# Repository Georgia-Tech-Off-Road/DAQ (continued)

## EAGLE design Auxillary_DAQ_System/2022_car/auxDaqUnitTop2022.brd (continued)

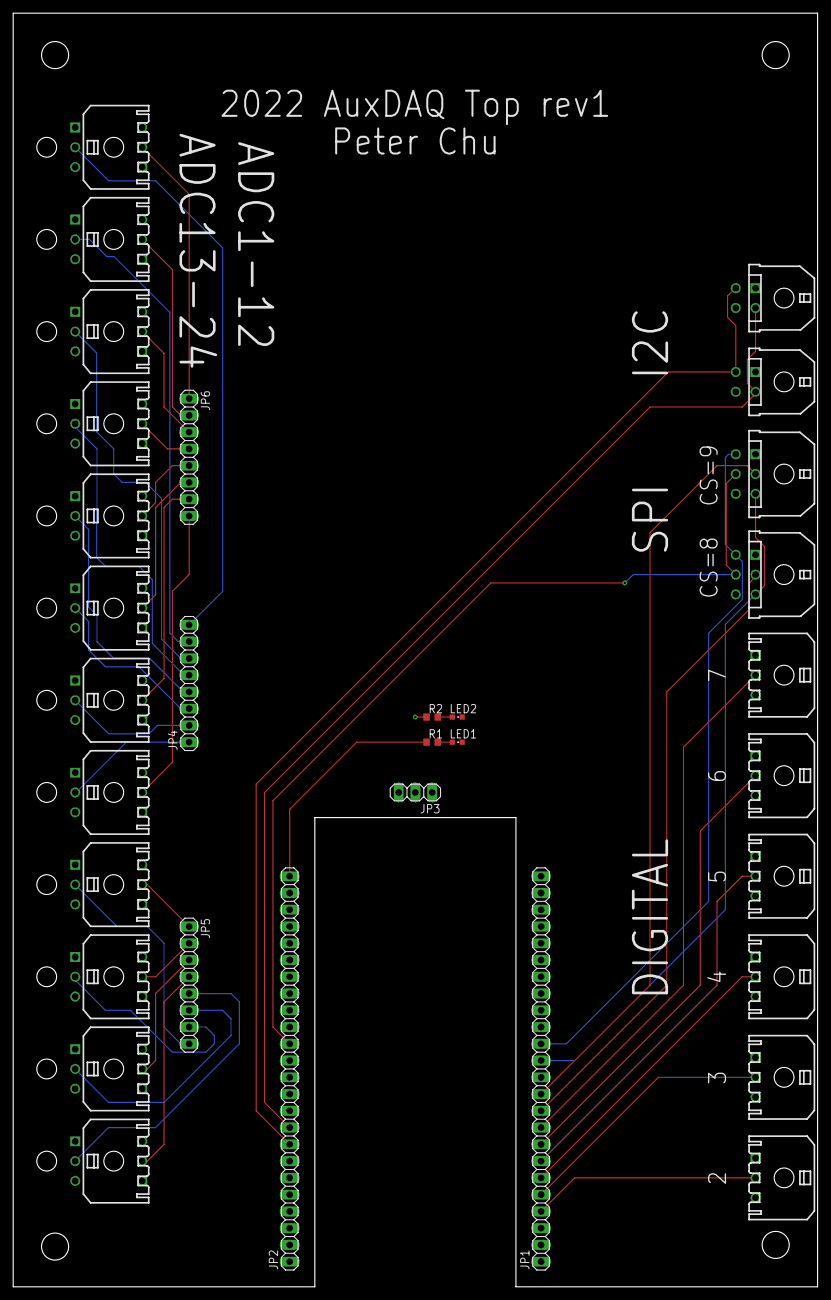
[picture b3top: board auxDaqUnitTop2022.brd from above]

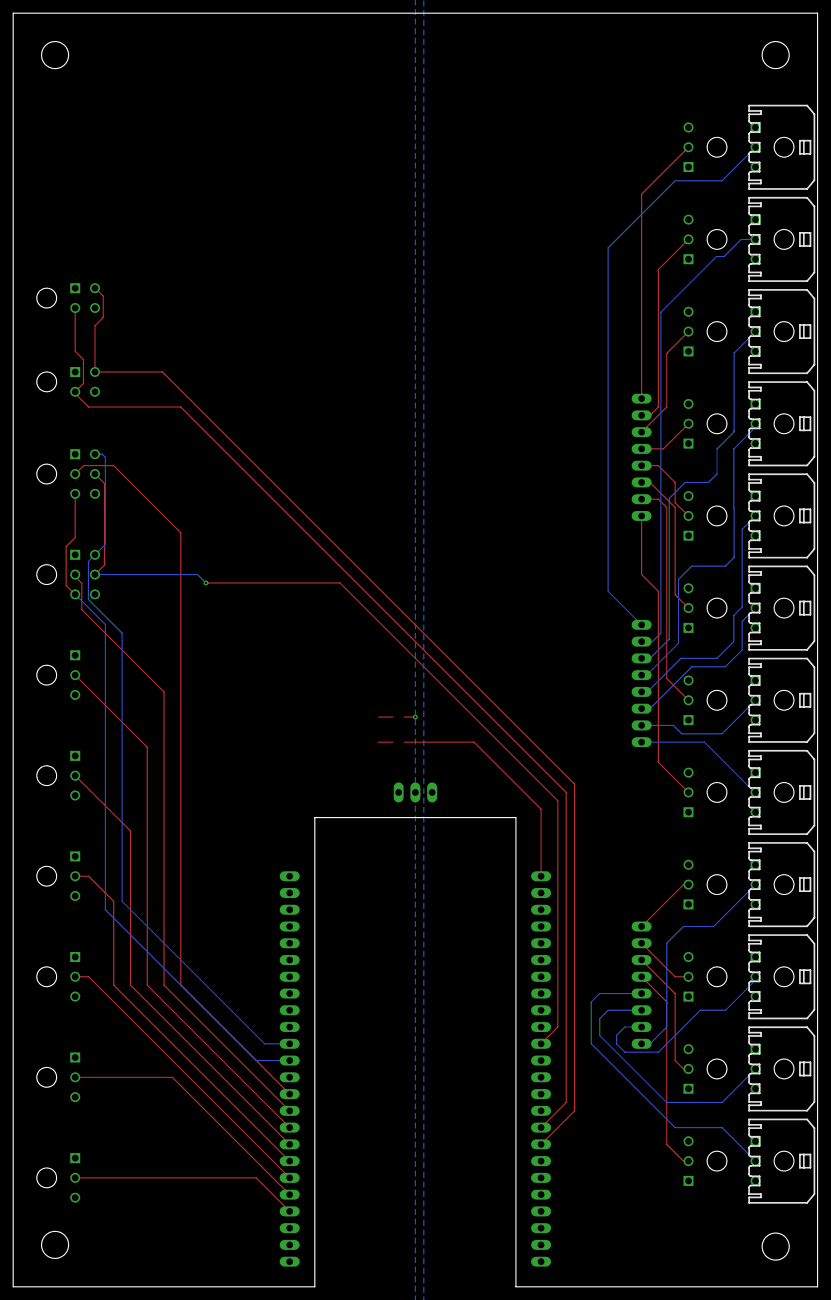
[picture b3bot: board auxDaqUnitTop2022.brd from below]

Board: 2 copper layers, 121.9 x 193.0 mm, 44 parts (12 on the bottom side), 43 nets.

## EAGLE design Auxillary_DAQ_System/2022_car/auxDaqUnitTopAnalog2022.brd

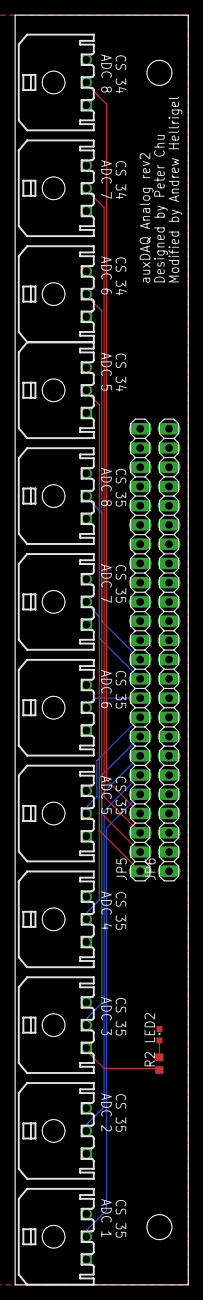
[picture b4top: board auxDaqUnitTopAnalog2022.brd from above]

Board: 2 copper layers, 22.9 x 167.6 mm, 16 parts (0 on the bottom side), 15 nets.

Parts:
A12, A13, A14, A15, A16, A17, A18, A19, A20, A21, A22, A23: 43650-0300
JP5, JP6: 1X24
LED2: GREEN; LED-603
R2: 220; R0603

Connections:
+5V: A12.P$1, A13.P$1, A14.P$1, A15.P$1, A16.P$1, A17.P$1, A18.P$1, A19.P$1, A20.P$1, A21.P$1, A22.P$1, A23.P$1, JP6.1, R2.1
ADC13: A12.P$2, JP5.1
ADC14: A13.P$2, JP5.2
ADC15: A14.P$2, JP5.3
ADC16: A15.P$2, JP5.4
ADC17: A16.P$2, JP5.5
ADC18: A17.P$2, JP5.6
ADC19: A18.P$2, JP5.7
ADC20: A19.P$2, JP5.8
ADC21: A20.P$2, JP5.9
ADC22: A21.P$2, JP5.10
ADC23: A22.P$2, JP5.11
ADC24: A23.P$2, JP5.12
GND: A12.P$3, A13.P$3, A14.P$3, A15.P$3, A16.P$3, A17.P$3, A18.P$3, A19.P$3, A20.P$3, A21.P$3, A22.P$3, A23.P$3, JP6.2, JP6.15, LED2.C
unnamed: LED2.A, R2.2

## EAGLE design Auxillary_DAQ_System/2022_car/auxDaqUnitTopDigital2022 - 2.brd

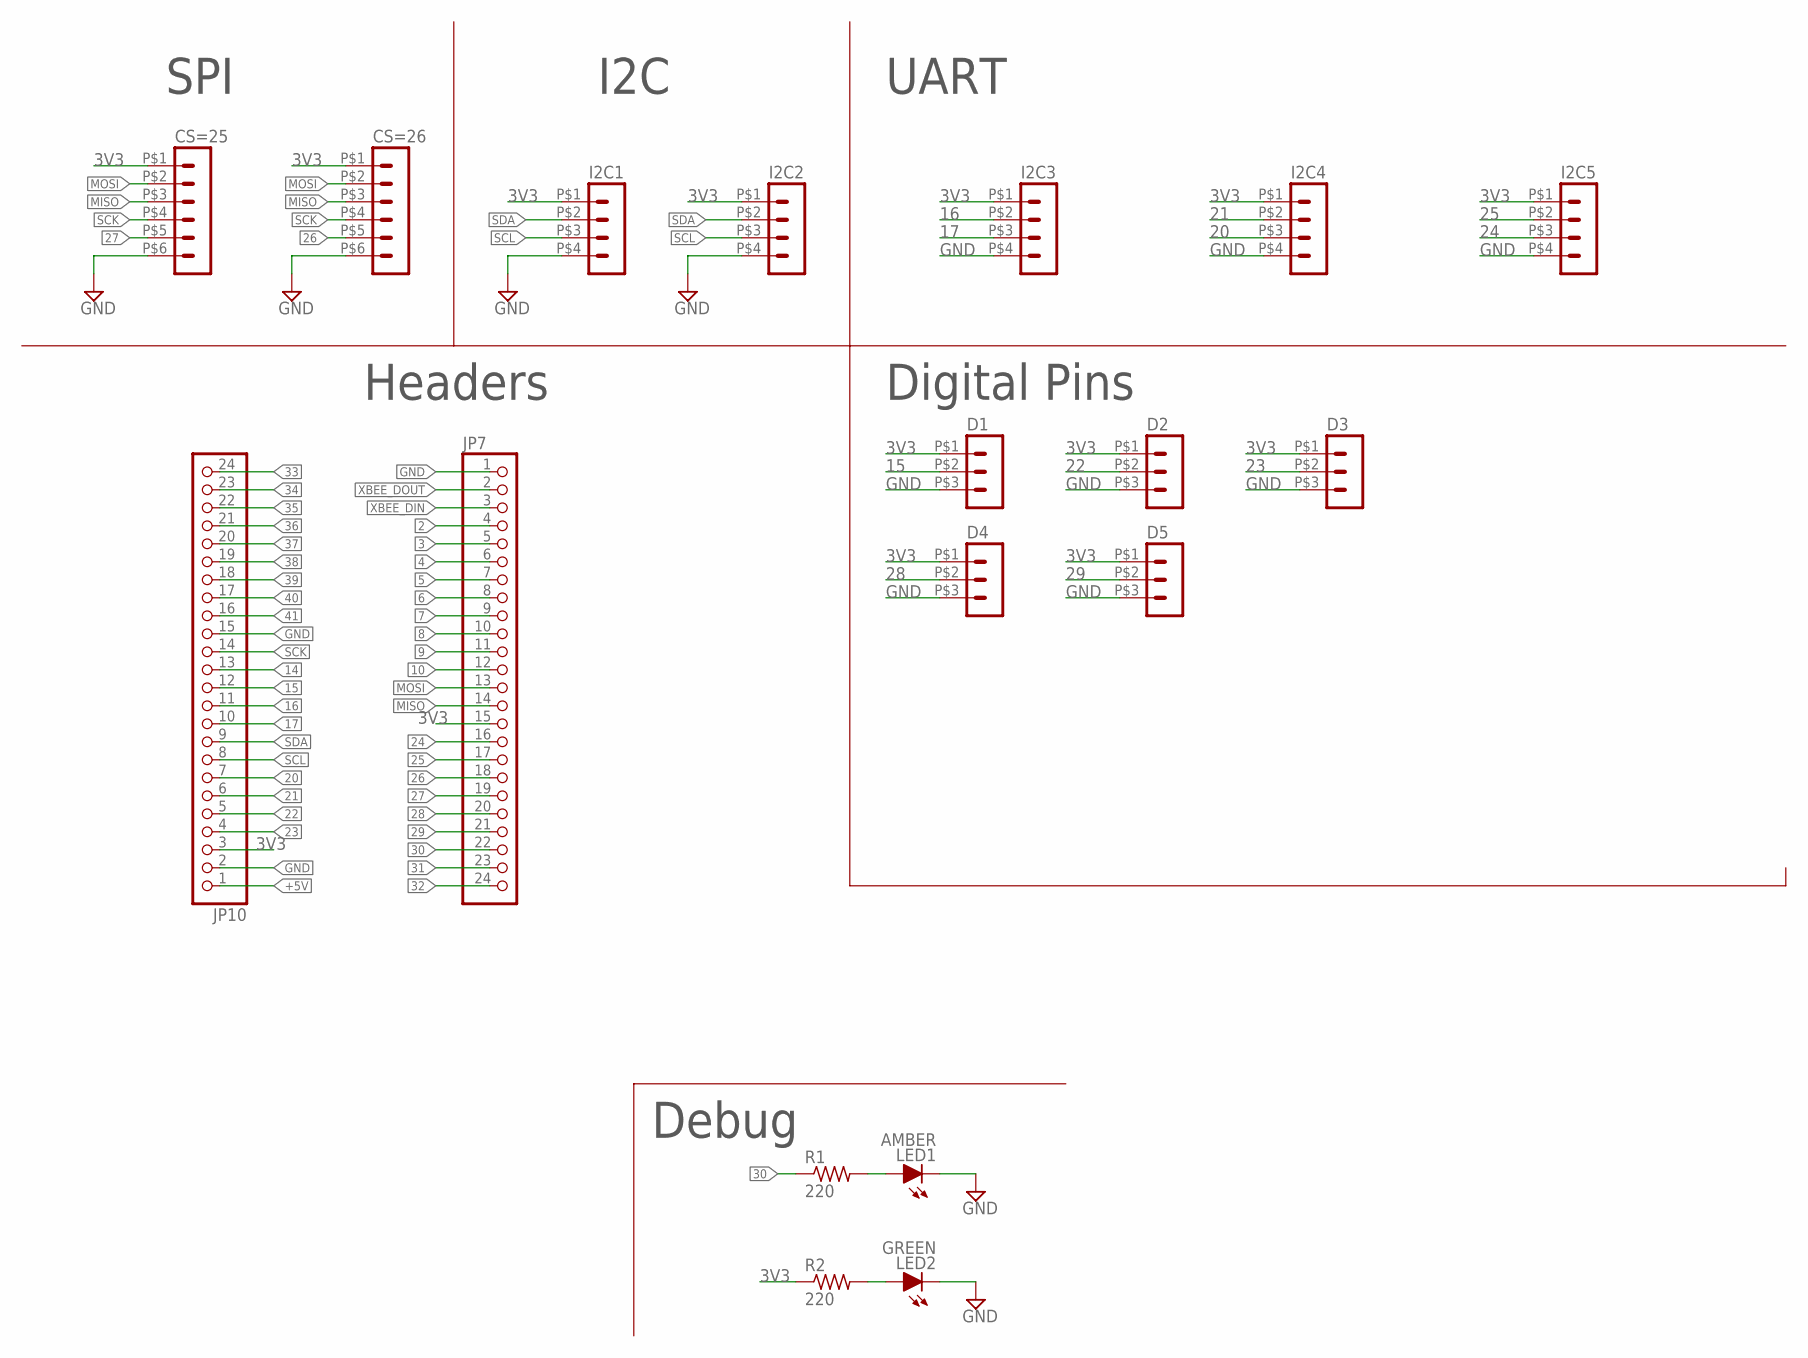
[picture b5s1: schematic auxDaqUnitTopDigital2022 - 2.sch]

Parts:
CS=25, CS=26: HEADER_POS6_43045-0600; 43045-0600
D1, D2, D3, D4, D5: HEADER_POS3_43650-0300; 43650-0300
I2C1, I2C2, I2C3, I2C4, I2C5: HEADER_POS4_43045-0401; 43045-0400
JP7, JP10: PINHD-1X24; 1X24
LED1: AMBER; LED-603
LED2: GREEN; LED-603
R1, R2: 220; R0603

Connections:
2: JP7.4
3: JP7.5
3V3: CS=25.P$1 (1), CS=26.P$1 (1), D1.P$1 (1), D2.P$1 (1), D3.P$1 (1), D4.P$1 (1), D5.P$1 (1), I2C1.P$1 (1), I2C2.P$1 (1), I2C3.P$1 (1), I2C4.P$1 (1), I2C5.P$1 (1), JP7.15, JP10.3, R2.1
4: JP7.6
5: JP7.7
6: JP7.8
7: JP7.9
8: JP7.10
9: JP7.11
10: JP7.12
14: JP10.13
15: D1.P$2 (2), JP10.12
16: I2C3.P$2 (2), JP10.11
17: I2C3.P$3 (3), JP10.10
20: I2C4.P$3 (3), JP10.7
21: I2C4.P$2 (2), JP10.6
22: D2.P$2 (2), JP10.5
23: D3.P$2 (2), JP10.4
24: I2C5.P$3 (3), JP7.16
25: I2C5.P$2 (2), JP7.17
26: CS=26.P$5 (5), JP7.18
27: CS=25.P$5 (5), JP7.19
28: D4.P$2 (2), JP7.20
29: D5.P$2 (2), JP7.21
30: JP7.22, R1.1
31: JP7.23
32: JP7.24
33: JP10.24
34: JP10.23
35: JP10.22
36: JP10.21
37: JP10.20
38: JP10.19
39: JP10.18
40: JP10.17
41: JP10.16
+5V: JP10.1
GND: CS=25.P$6 (6), CS=26.P$6 (6), D1.P$3 (3), D2.P$3 (3), D3.P$3 (3), D4.P$3 (3), D5.P$3 (3), I2C1.P$4 (4), I2C2.P$4 (4), I2C3.P$4 (4), I2C4.P$4 (4), I2C5.P$4 (4), JP7.1, JP10.2, JP10.15, LED1.C, LED2.C
MISO: CS=25.P$3 (3), CS=26.P$3 (3), JP7.14
MOSI: CS=25.P$2 (2), CS=26.P$2 (2), JP7.13
unnamed: LED1.A, R1.2
unnamed: LED2.A, R2.2
SCK: CS=25.P$4 (4), CS=26.P$4 (4), JP10.14
SCL: I2C1.P$3 (3), I2C2.P$3 (3), JP10.8
SDA: I2C1.P$2 (2), I2C2.P$2 (2), JP10.9
XBEE_DIN: JP7.3
XBEE_DOUT: JP7.2

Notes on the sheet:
Headers
SPI
I2C
Digital Pins
Debug
UART

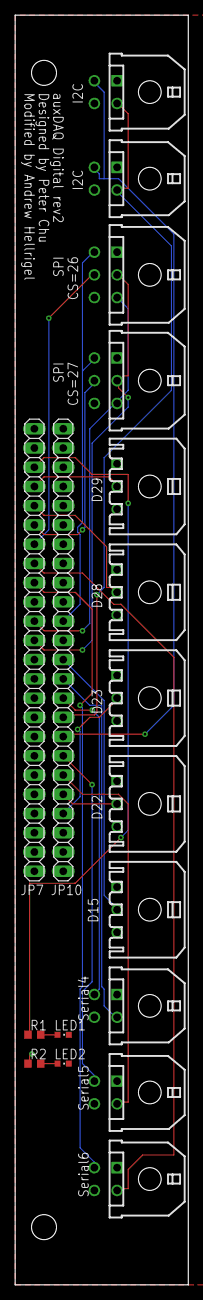
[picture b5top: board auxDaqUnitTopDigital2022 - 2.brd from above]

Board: 2 copper layers, 22.9 x 167.6 mm, 18 parts (0 on the bottom side), 23 nets.

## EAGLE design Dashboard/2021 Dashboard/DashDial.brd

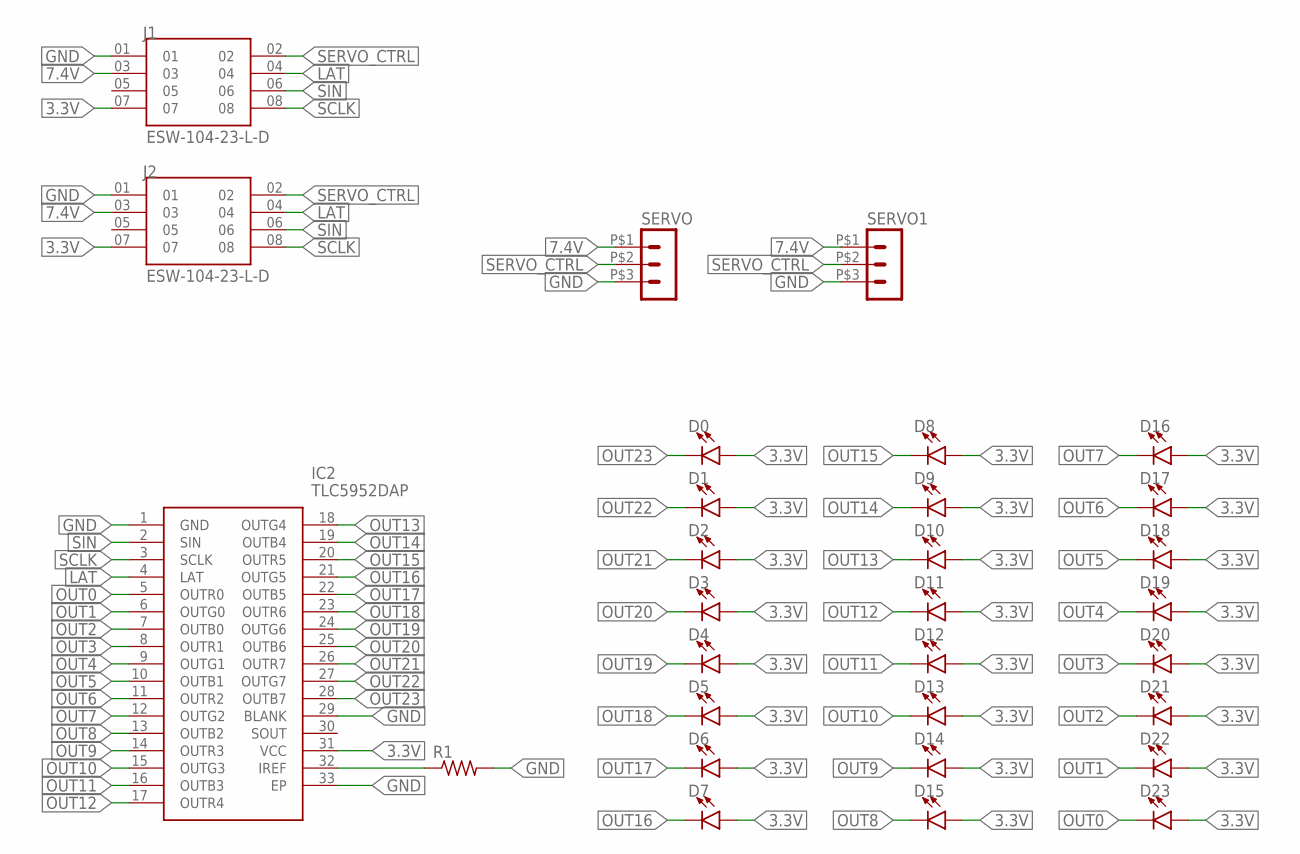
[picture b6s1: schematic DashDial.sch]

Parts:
D0, D1, D2, D3, D4, D5, D6, D7, D8, D9, D10, D11, D12, D13, D14, D15, D16, D17, D18, D19, D20, D21, D22, D23: LED3MM; LED_3MM
IC2: TLC5952DAP; SOP65P810X120-33N
J1, J2: ESW-104-23-L-D; SAMTEC_ESW-104-23-L-D
R1: RES_SMDR0603; R0603
SERVO, SERVO1: HEADER_POS3_43650-0300; 43650-0300

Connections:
3.3V: D0.A, D1.A, D2.A, D3.A, D4.A, D5.A, D6.A, D7.A, D8.A, D9.A, D10.A, D11.A, D12.A, D13.A, D14.A, D15.A, D16.A, D17.A, D18.A, D19.A, D20.A, D21.A, D22.A, D23.A, IC2.31 (VCC), J1.07, J2.07
7.4V: J1.03, J2.03, SERVO.P$1 (1), SERVO1.P$1 (1)
GND: IC2.1 (GND), IC2.29 (BLANK), IC2.33 (EP), J1.01, J2.01, R1.2, SERVO.P$3 (3), SERVO1.P$3 (3)
LAT: IC2.4 (LAT), J1.04, J2.04
unnamed: IC2.32 (IREF), R1.1
OUT0: D23.K (C), IC2.5 (OUTR0)
OUT1: D22.K (C), IC2.6 (OUTG0)
OUT2: D21.K (C), IC2.7 (OUTB0)
OUT3: D20.K (C), IC2.8 (OUTR1)
OUT4: D19.K (C), IC2.9 (OUTG1)
OUT5: D18.K (C), IC2.10 (OUTB1)
OUT6: D17.K (C), IC2.11 (OUTR2)
OUT7: D16.K (C), IC2.12 (OUTG2)
OUT8: D15.K (C), IC2.13 (OUTB2)
OUT9: D14.K (C), IC2.14 (OUTR3)
OUT10: D13.K (C), IC2.15 (OUTG3)
OUT11: D12.K (C), IC2.16 (OUTB3)
OUT12: D11.K (C), IC2.17 (OUTR4)
OUT13: D10.K (C), IC2.18 (OUTG4)
OUT14: D9.K (C), IC2.19 (OUTB4)
OUT15: D8.K (C), IC2.20 (OUTR5)
OUT16: D7.K (C), IC2.21 (OUTG5)
OUT17: D6.K (C), IC2.22 (OUTB5)
OUT18: D5.K (C), IC2.23 (OUTR6)
OUT19: D4.K (C), IC2.24 (OUTG6)
OUT20: D3.K (C), IC2.25 (OUTB6)
OUT21: D2.K (C), IC2.26 (OUTR7)
OUT22: D1.K (C), IC2.27 (OUTG7)
OUT23: D0.K (C), IC2.28 (OUTB7)
SCLK: IC2.3 (SCLK), J1.08, J2.08
SERVO_CTRL: J1.02, J2.02, SERVO.P$2 (2), SERVO1.P$2 (2)
SIN: IC2.2 (SIN), J1.06, J2.06

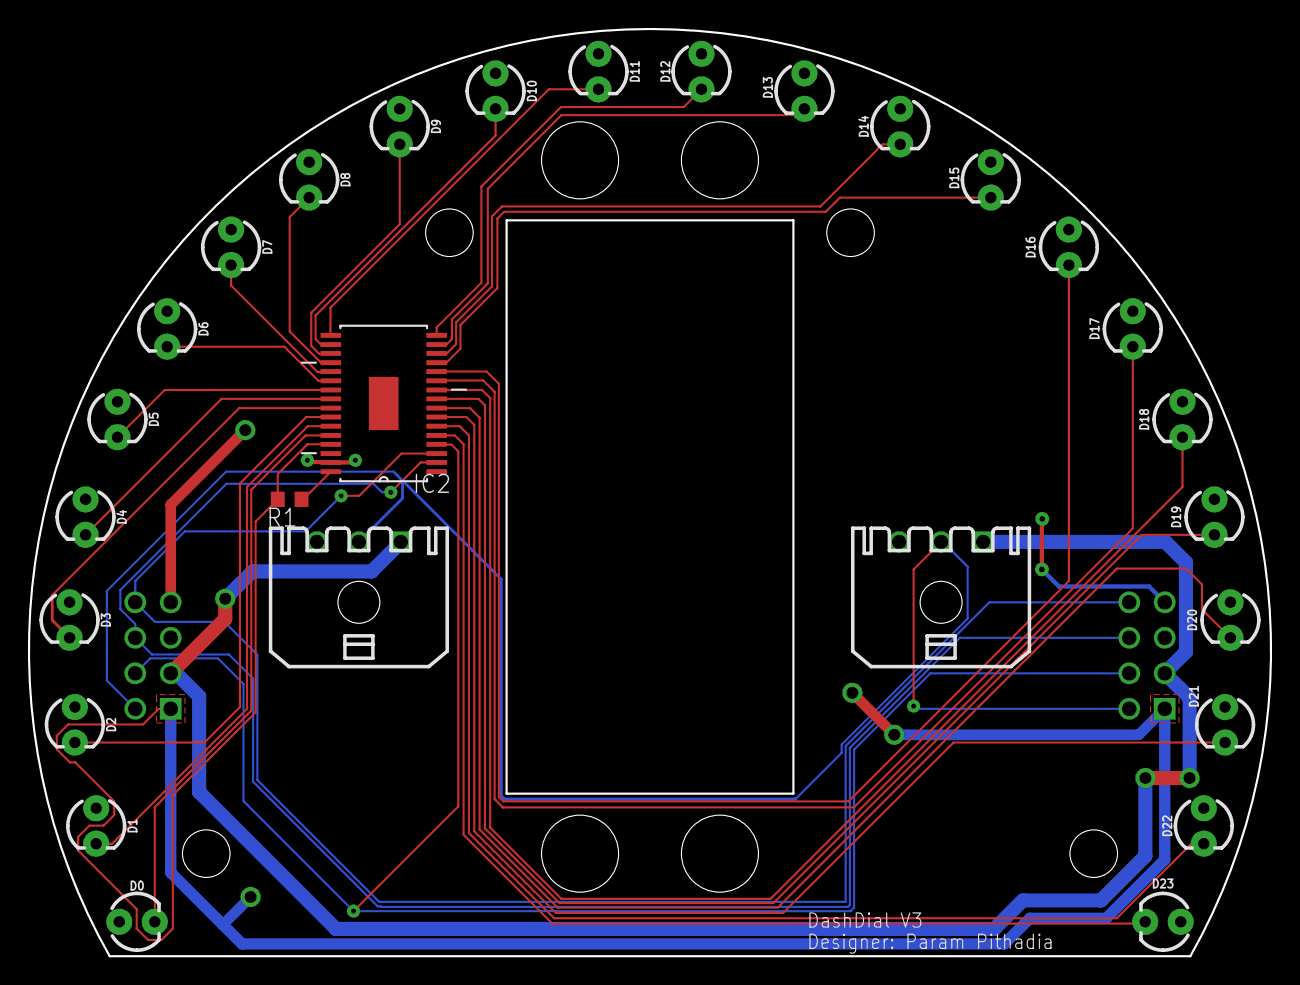
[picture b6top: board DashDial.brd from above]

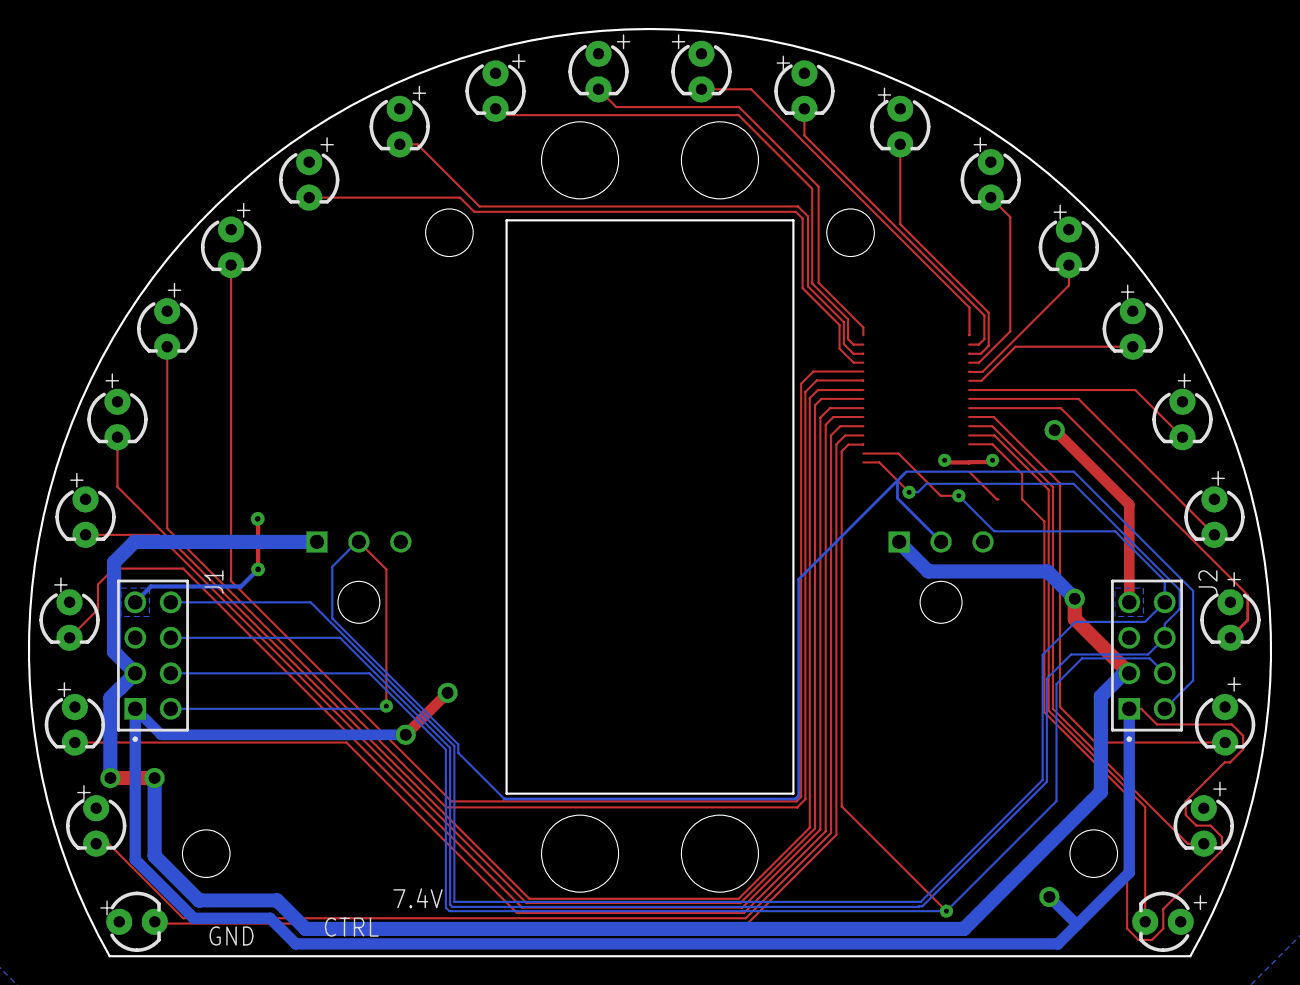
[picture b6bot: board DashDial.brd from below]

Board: 2 copper layers, 88.9 x 66.3 mm, 30 parts (2 on the bottom side), 32 nets.

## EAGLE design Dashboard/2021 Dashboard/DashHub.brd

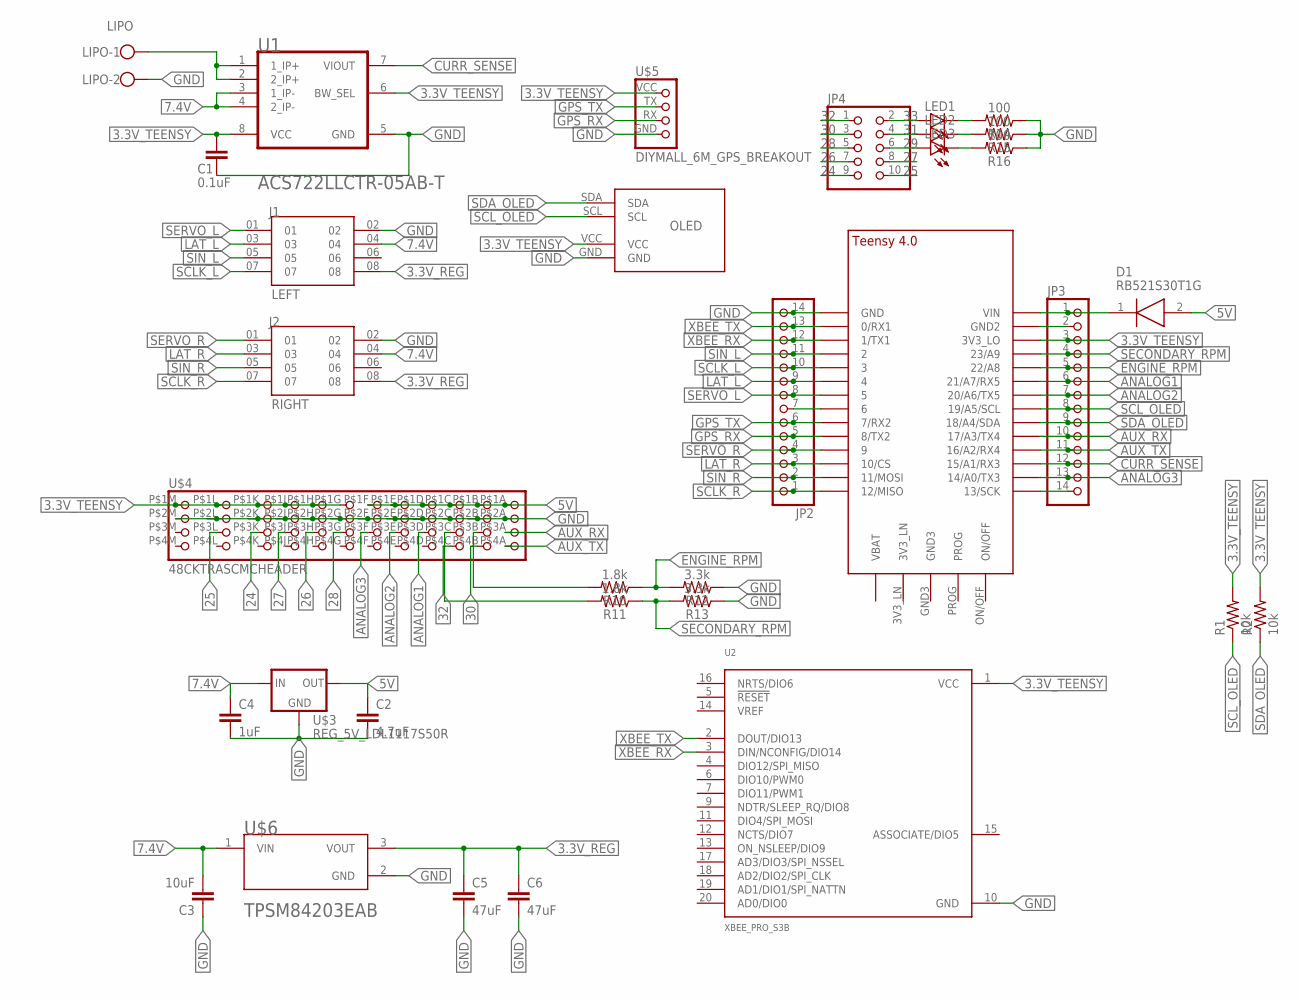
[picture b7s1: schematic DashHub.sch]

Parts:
C1: 0.1uF; C0402
C2: 4.7uF; C0603
C3: 10uF; C1206
C4: 1uF; C1206
C5, C6: 47uF; C1206
D1: RB521S30T1G; SODFL1608X70N
J1: LEFT; SAMTEC_ESW-104-23-L-D
J2: RIGHT; SAMTEC_ESW-104-23-L-D
JP2, JP3: PINHD-1X14; 1X14
JP4: PINHD-2X5; 2X05
LED1, LED2, LED3: LEDCHIPLED_1206; CHIPLED_1206
LIPO: LIPO; W237-102
R1, R2: 10k; R0603
R10, R11: 1.8k; AXIAL-0.3
R12, R13: 3.3k; AXIAL-0.3
R14, R15, R16: 100; AXIAL-0.3
U1: ALLEGRO_MICROSYSTEMS_ACS722LLCTR-05AB-TALLEGRO_MI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; ALLEGRO_MICROSYSTEMS_ACS722LLCTR-05AB-T_0
U2: XBEE_PRO_S3B
U$1: TEENSY_4.0-BASIC
U$2: OLED_SSD1306
U$3: REG_5V_LDL1117S50R; SOT230P700X180-4N
U$4: 48CKTRASCMCHEADER
U$5: DIYMALL_6M_GPS_BREAKOUT
U$6: TPSM84205EAB

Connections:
3.3V_REG: C5.1, C6.1, J1.08, J2.08, U$6.3 (VOUT)
3.3V_TEENSY: C1.2, JP3.3, R1.2, R2.2, U1.6 (BW_SEL), U1.8 (VCC), U2.1 (VCC), U$1.3V3_LO, U$2.VCC, U$4.P$1G (1G), U$4.P$1H (1H), U$4.P$1J (1J), U$4.P$1K (1K), U$4.P$1L (1L), U$4.P$1M (1M), U$5.VCC
5V: C2.1, D1.2 (A), U$3.2 (OUT), U$3.4 (OUT), U$4.P$1A (1A), U$4.P$1B (1B), U$4.P$1C (1C), U$4.P$1D (1D), U$4.P$1E (1E), U$4.P$1F (1F)
7.4V: C3.2, C4.1, J1.04, J2.04, U1.3 (1_IP-), U1.4 (2_IP-), U$3.3 (IN), U$6.1 (VIN)
24: JP4.9, U$4.P$3K (3K)
25: JP4.10, U$4.P$3L (3L)
26: JP4.7, U$4.P$3H (3H)
27: JP4.8, U$4.P$3J (3J)
28: JP4.5, U$4.P$3G (3G)
29: JP4.6, LED3.A
30: JP4.3, U$4.P$4B (4B)
31: JP4.4, LED2.A
32: JP4.1, U$4.P$4C (4C)
33: JP4.2, LED1.A
ANALOG1: JP3.6, U$1.21/A7 (21/A7/RX5), U$4.P$3D (3D)
ANALOG2: JP3.7, U$1.20/A6 (20/A6/TX5), U$4.P$3E (3E)
ANALOG3: JP3.13, U$1.14/A0 (14/A0/TX3), U$4.P$3F (3F)
AUX_RX: JP3.10, U$1.17/A3 (17/A3/TX4), U$4.P$3A (3A)
AUX_TX: JP3.11, U$1.16/A2 (16/A2/RX4), U$4.P$4A (4A)
CURR_SENSE: JP3.12, U1.7 (VIOUT), U$1.15/A1 (15/A1/RX3)
ENGINE_RPM: JP3.5, R10.P$1 (1), R12.P$2 (2), U$1.22/A8
GND: C1.1, C2.2, C3.1, C4.2, C5.2, C6.2, J1.02, J2.02, JP2.14, LIPO.2, R12.P$1 (1), R13.P$1 (1), R14.P$1 (1), R15.P$1 (1), R16.P$1 (1), U1.5 (GND), U2.10 (GND), U$1.GND, U$2.GND, U$3.1 (GND), U$4.P$2A (2A), U$4.P$2B (2B), U$4.P$2C (2C), U$4.P$2D (2D), U$4.P$2E (2E), U$4.P$2F (2F), U$4.P$2G (2G), U$4.P$2H (2H), U$4.P$2J (2J), U$4.P$2K (2K), U$4.P$2L (2L), U$4.P$2M (2M), U$5.GND, U$6.2 (GND)
GND2: JP3.2, U$1.GND2
GPS_RX: JP2.5, U$1.8 (8/TX2), U$5.RX
GPS_TX: JP2.6, U$1.7 (7/RX2), U$5.TX
LAT_L: J1.03, JP2.9, U$1.4/CANRX (4)
LAT_R: J2.03, JP2.3, U$1.10/CS
LIPO_IN: LIPO.1, U1.1 (1_IP+), U1.2 (2_IP+)
unnamed: JP2.7, U$1.6
unnamed: D1.1 (K), JP3.1, U$1.VIN
unnamed: LED1.C, R14.P$2 (2)
unnamed: LED2.C, R15.P$2 (2)
unnamed: LED3.C, R16.P$2 (2)
unnamed: R10.P$2 (2), U$4.P$3B (3B)
unnamed: R11.P$2 (2), U$4.P$3C (3C)
SCLK_D: JP3.14, U$1.13/SCK
SCLK_L: J1.07, JP2.10, U$1.3/CANTX (3)
SCLK_R: J2.07, JP2.1, U$1.12/MISO
SCL_OLED: JP3.8, R1.1, U$1.19/A5/SCL, U$2.SCL
SDA_OLED: JP3.9, R2.1, U$1.18/A4/SDA, U$2.SDA
SECONDARY_RPM: JP3.4, R11.P$1 (1), R13.P$2 (2), U$1.23/A9
SERVO_L: J1.01, JP2.8, U$1.5
SERVO_R: J2.01, JP2.4, U$1.9/CS (9)
SIN_L: J1.05, JP2.11, U$1.2
SIN_R: J2.05, JP2.2, U$1.11/MOSI
XBEE_RX: JP2.12, U2.3 (DIN/NCONFIG/DIO14), U$1.1/TX (1/TX1)
XBEE_TX: JP2.13, U2.2 (DOUT/DIO13), U$1.0/RX (0/RX1)

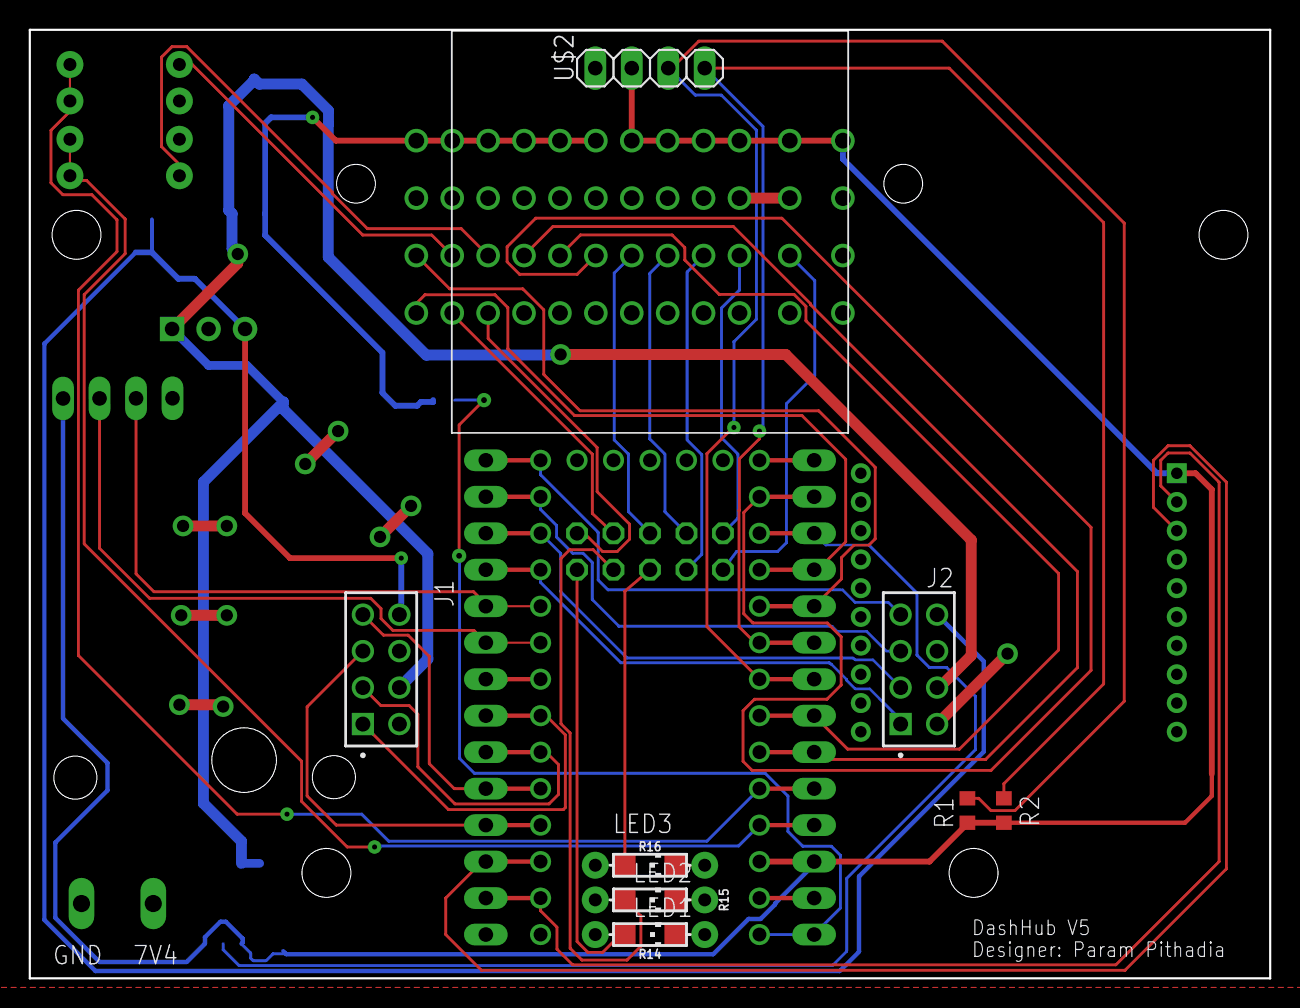
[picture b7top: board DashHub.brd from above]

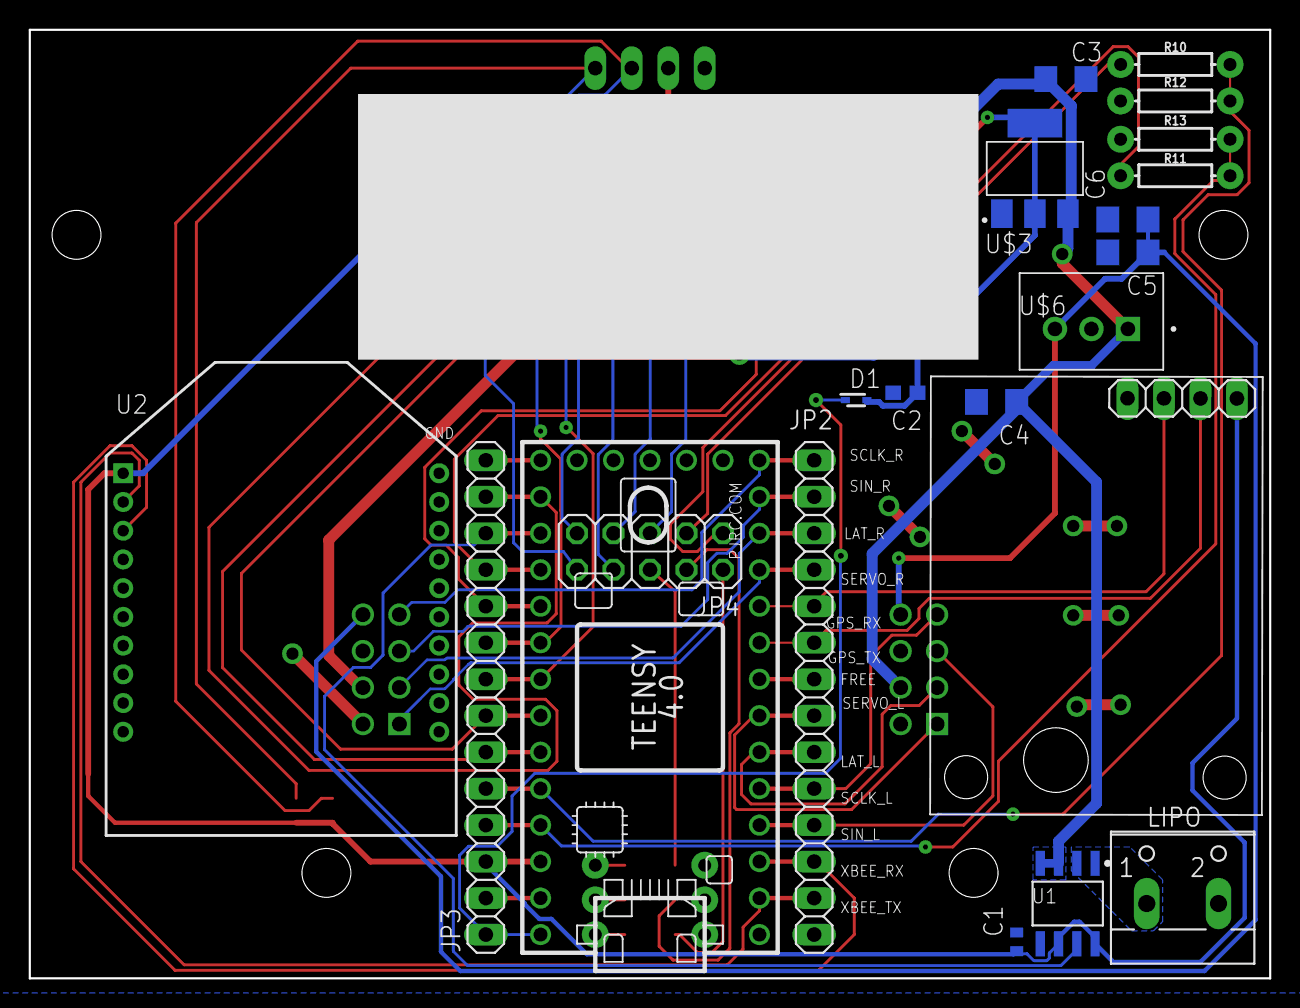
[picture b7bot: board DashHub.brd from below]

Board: 2 copper layers, 86.4 x 66.0 mm, 33 parts (22 on the bottom side), 47 nets.

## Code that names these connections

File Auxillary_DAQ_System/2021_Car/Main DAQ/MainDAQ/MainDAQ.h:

#ifndef MAIN_DAQ_H
#define MAIN_DAQ_H

#include <Arduino.h>
#include "HallEffectSpeedSensor.h"
#include "BrakePressureTransducer.h"

#define THREEV3DIG_1 14
#define THREEV3DIG_2 5
#define THREEV3DIG_3 16
#define THREEV3DIG_4 6
#define THREEV3DIG_5 15
#define THREEV3DIG_6 2
#define THREEV3DIG_7 38
#define THREEV3DIG_8 3

#define RX_1 17
#define RX_2 39

#define THREEV3ANA_1 9
#define THREEV3ANA_2 22
#define THREEV3ANA_3 33
#define THREEV3ANA_4 23
#define THREEV3ANA_5 7
#define THREEV3ANA_6 4
#define THREEV3ANA_7 40
#define THREEV3ANA_8 32
#define THREEV3ANA_9 41
#define THREEV3ANA_10 8

#define SDA 18
#define SCL 19

#define MISO 12
#define MOSI 11
#define CS_1 13
#define CS_2 24
#define CS_3 25
#define CS_4 26
#define CS_5 27
#define CS_6 28
#define CS_7 29

#define FIVEVDIG_1 31
#define FIVEVDIG_2 30
#define FIVEVDIG_3 20
#define FIVEVDIG_4 21

////// FIND THE PIN NUMBERS FOR THESE OR SOMESTHINGS
// #define 5VANA_1 AIN0
// #define 5VANA_2 AIN2
// #define 5VANA_3 AIN1
// #define 5VANA_4 AIN3

// 3V3 Dig Pins (5, 2, 6, 3, 8, 4, 32, 33)

// TX (8) RX (7)

// 3V3 Analog Pins (14, 15, 16, 38, 17, 39, 22, 40, 23, 41)

// SDA (18) SDL (19)

// MISO (12), MOSI (11), CS (13, 24, 25, 26, 27, 28, 29)

// 5V Dig Pins (31, 20, 30, 21)

// 5V Analog Pins (AIN1-4) 

#endif
